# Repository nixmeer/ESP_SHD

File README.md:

# ESP_SmartHomeDevice
Keep it simple and stupid. Everyone should be able to build his or her smart home device (SHD).
## What this project is supposed to do:
This code runs on ESP8266 and is optimized to work together with [HomeBridge](https://github.com/nfarina/homebridge) and [mqttthing](https://github.com/arachnetech/homebridge-mqttthing)
- [x] create an easy to use platform that uses wifi and mqtt to talk to [mqttthing](https://github.com/arachnetech/homebridge-mqttthing)
- [ ] print json-config-code for homebridge-mqttthing
- [ ] create a webserver and a settings class that allow setup via GUI
## Supported devices
- [x] Stateless switches
- [x] TMP36 sensors
- [x] DHT22 temperature and humidity sensors
- [x] Motion sensors
- [x] Single color PWM light
- [x] Temperature PWM light
- [x] WS2512b strips
- [x] Sprinkler
- [x] Relay/Switch
- [x] Window blinds
## Libraries and cores used
- [Arduino core for ESP8266 WiFi chip](https://github.com/esp8266/Arduino) (v2.4.2)
- [pubSubClient](https://github.com/knolleary/pubsubclient) by knolleary (v2.7.0)
- [FastLED](https://github.com/FastLED/FastLED) by FastLED (v3.3.2)
- [WiFiManager](https://github.com/tzapu/WiFiManager) by tzapu (v0.15.0)
- [ESP8266_new_pwm](https://github.com/StefanBruens/ESP8266_new_pwm) by StefanBruens (included)
## Code Structure
There is a separate class for each device. Every device is implemented as a child class of ESP_SmartHomeDevice. After initializing ESP_SmartHomeDevice, objects of these classes may be created. All of these objects use one common mqtt client provided by ESP_SmartHomeDevice. Each child class of ESP_SmartHomeDevice has to implement the following member functions:
- `bool handleMqttRequest(char * _topic, unsigned char * _payload, uint16_t _length)` is being called after a request has been pushed to the mqtt client
- `void resubscribe()` is being called after the connection to the mqtt broker was lost
- `void timer5msHandler()` is being called every 5 ms
## Basic usage in Arduino
```
ESP_SmartHomeDevice::init(const char* _mqttServerAddress, uint16_t _port, char* _name);
ESP_SmartHomeDevice::init(char* _name)
```
Call `ESP_SmartHomeDevice::init(...)` to setup and initialize wifi and mqtt in the `setup()` function of your *.ino* file. If there is no known wifi network, a wifi access point will be created which lets you connect the ESP to a wifi network. If you use **one** local mqtt broker and it is discoverable via mDNS, call `ESP_SmartHomeDevice::init(char* _name)`. The SHD then automatically connects to it. If it discovers 0 or more than one, it resets itself.
Now just create new devices using `new Shd...()`.
MQTT topics do always begin with the `_name` parameter initialized here.
## Creating devices
### Motion Sensor
To add a motion sensor, just call `new ShdMotionSensor(uint8_t _pin)`. It publishes it's status (`true` or `false` as char) to `_name/Motion`.
### Temperature Sensor
To add a temperature sensor, just call `new ShdTmp36Sensor()`. No pin is needed, since there is only one ADC available in the ESP8266. It publishes the temperature to `_name/Temperature`.
### WS2812b strip
Only stips at pin 4 are Supported.
Call ` ShdWs2812bStrip::initStrip(uint16_t _numberOfLeds, uint16_t _updateInterval)`. First argument sets the number of LEDs of the entire strip, second argument sets the update interval for the strip in milliseconds. 41 ms (24 fps) looked jerky, 25 ms (40 fps) looks much better.
Call `new ShdWs2812bStrip(uint16_t _firstLed, uint16_t _lastLed, uint16_t _ignitionPoint, ignitionDirection _ignitionDirection, uint8_t _hopsPerShow, uint8_t _flankLength)` to create a light section, multiple can be created for one strip and be used simultaneously. These sections can overlap (not yet tested).
- `_firstLed` is this section's first LED (value 1 or greater)
- `_lastLed` is this section's last LED (less or equal to `_numberOfLeds`)
- `_ignitionPoint` is the LED that all effects start from
- `_ignitionDirection` is `IGNITION_SINGLE_FORWARD`, `IGNITION_SINGLE_BACKWARD`, `IGNITION_BOTH_FORWARD` or `IGNITION_BOTH_BACKWARD`
- `_hopsPerShow` is the number of LEDs that the turn-on effect is shifted each frame. This has an impact on the effects speed.
- `_flankLength` sets the number of LEDs that are needed to transfer from one color to another
ShdWs2812bStrip subscribes to `_name/Lamp/_sectionNumber/setColor` and `_name/Lamp/_sectionNumber/setStatus`. `_sectionNumber`is increased for every new section starting at 1.
ShdWs2812bStrip publishes its status (0 and 1) to `_name/Lamp/_sectionNumber/getStatus`, its color to `_name/Lamp/_sectionNumber/getColor` and publishes its brightness to `_name/Lamp/_sectionNumber/getBrightness`.
### Button
To add a new button, call `new ShdButton(uint8_t _pin, bool _lowActive, uint32_t _millisDebounce, uint32_t _millisLongClick, uint32_t _millisMultiClick)`. It publishes to `_name/Button/_buttonNumber`. It detects single clicks ("1"), double clicks("2") and long presses ("L"). `_buttonNumber` is increased for every new button starting at 1.
### Relay
To ad a new relay, use `new ShdRelay(uint8_t _pin, uint32_t _millisBetweenToggle, bool _lowActive)`. It subscribes `_name/Relay/_relayNumber/setStatus` where `_name` is the device name and `_relayNumber` counts the created relays starting at 1. It publishes its status to `_name/Relay/_relayNumber/getStatus`. `_millisBetweenToggle` sets the minimum time between to toggles avoiding the relay to be switched to quickly.
# Hardware
This repository contains the eagle and gerber files of my SHD hardware. The PCBs can be ordered from jlcpcb.com or any other pcb manufacturer. The following parts are necessary for a basic assembly:
- ESP12f module
- XC6206 voltage regulator
- 3 resistors (10k0)
- pinheader (7 pins)
To programm the ESP8266, you can use any 3.3 V FTDI board. I use the ESP01-flasher and created a adapter cable using jumper wires and heat shrink tubing. Note: most ESP01-flashers need to have a GND connection to GPIO 0 added to put the ESP8266 to flash mode.
# mosquitto broker on raspberry pi
You can use any mqtt broker with this code. In order to have all devices run stable and reconnect after a loss of power, it's recommended to use mDNS to expose the mqtt broker service to the network, so all SHDs can automatically connect to it. After installing mosquitto on the raspberry pi, call `sudo nano /etc/avahi/services/mqtt.service`. Fill the following:
```
<?xml version="1.0" standalone='no'?>
<!DOCTYPE service-group SYSTEM "avahi-service.dtd">
<service-group>
 <name replace-wildcards="yes">MQTT on %h</name>
  <service>
   <type>_mqtt._tcp</type>
   <port>1883</port>
  </service>
</service-group>
```
Then reboot. SHDs should find the broker now automatically.

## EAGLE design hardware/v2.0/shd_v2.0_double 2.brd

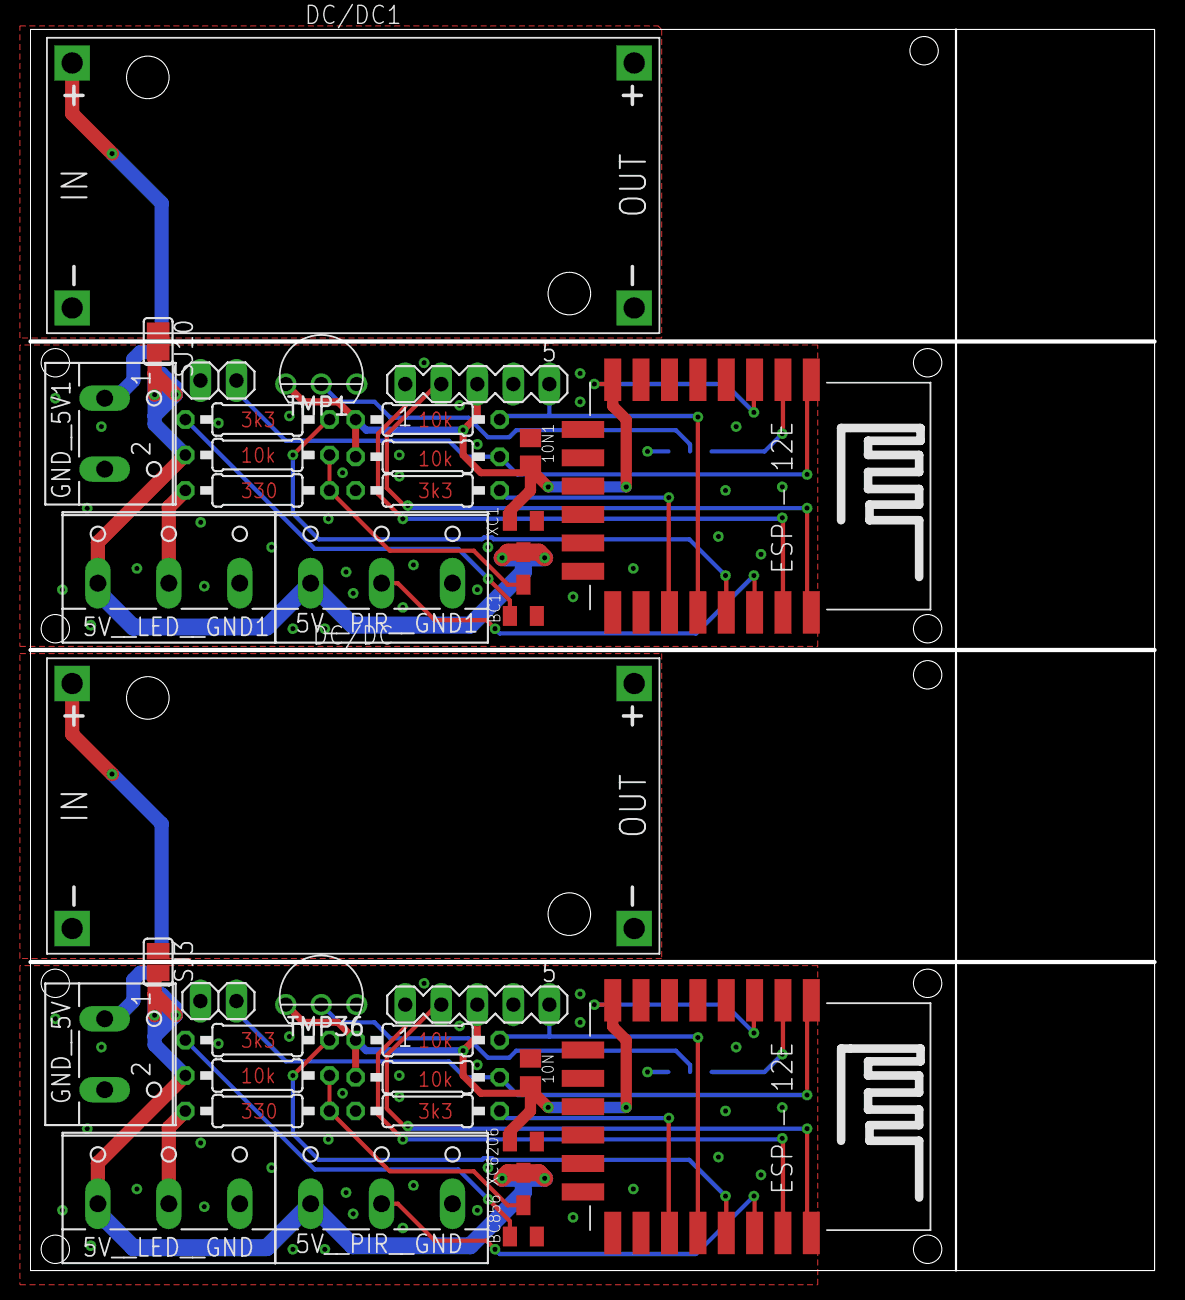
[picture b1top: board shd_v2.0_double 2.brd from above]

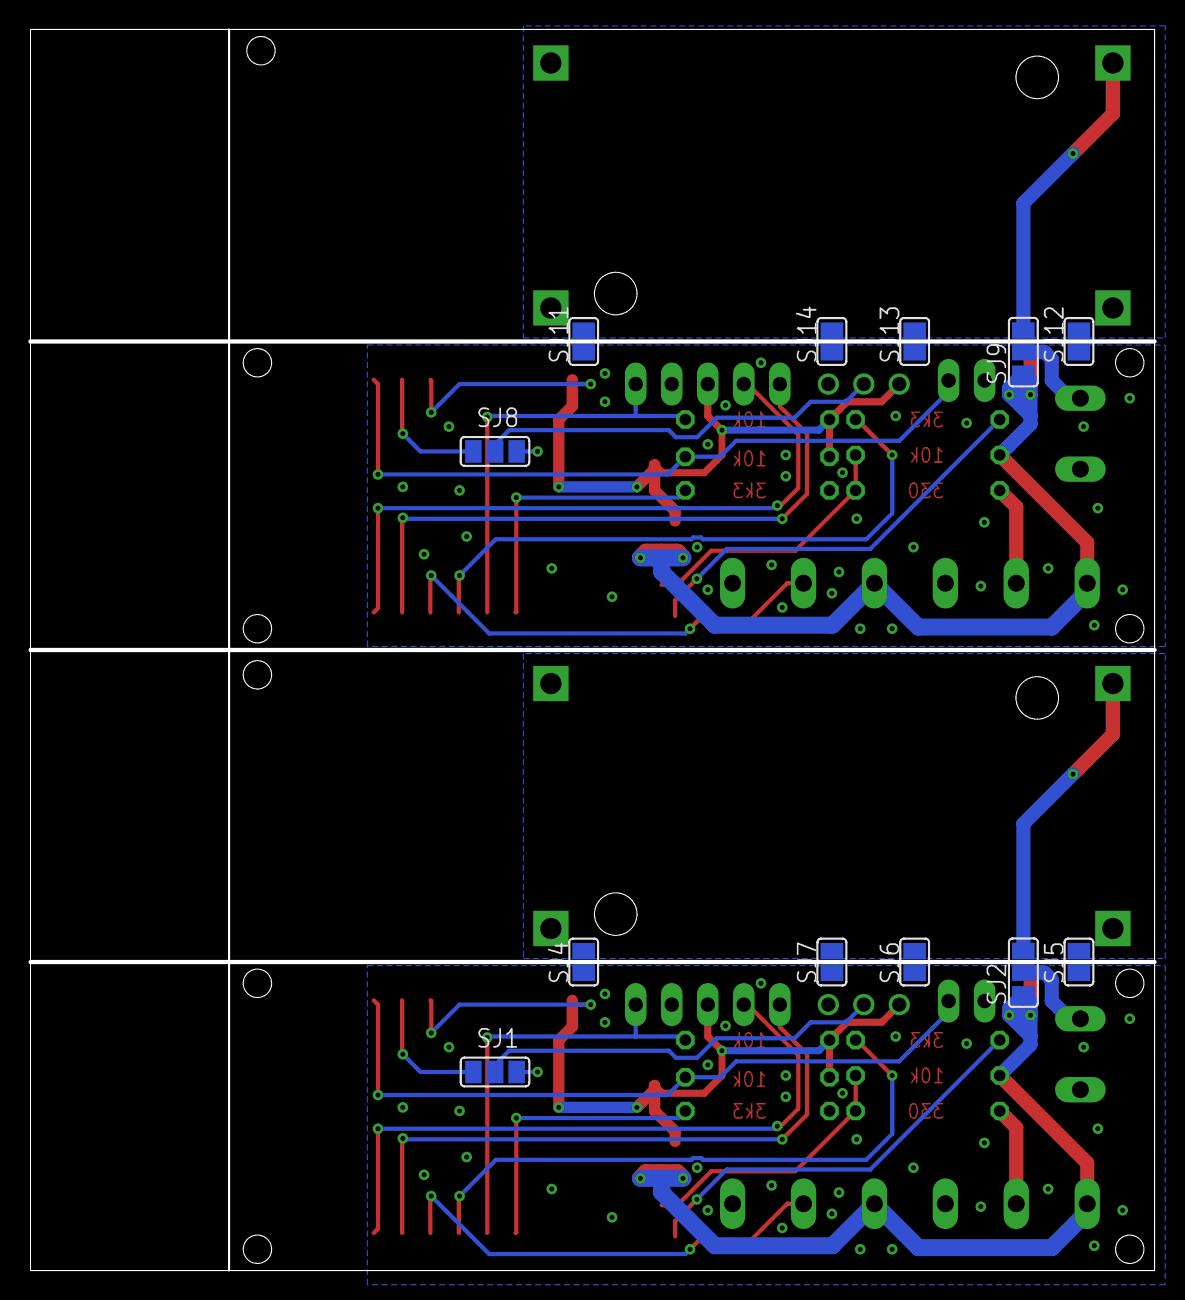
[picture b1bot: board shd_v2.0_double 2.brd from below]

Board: 2 copper layers, 79.2 x 87.4 mm, 48 parts (12 on the bottom side), 38 nets.

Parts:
5V__LED__GND, 5V__LED__GND1, 5V__PIR__GND, 5V__PIR__GND1: W237-103
10N, 10N1: C0805
BC1, BC856: SOT23-BEC
DC/DC, DC/DC1: DC-DC-STEP-DOWN-LM2596
GND__5V, GND__5V1: W237-102
JP1, JP2: 1X02
PROG_INTERFACE, PROG_INTERFACE1: MA05-1
R_GPIO1, R_GPIO2: 3k3; 0207/10
R_LED_B, R_LED_B1: 3k3; 0207/10
R_LED_C, R_LED_C2: 10k; 0207/10
R_LED_C1, R_LED_C3: 330; 0207/10
R_PROG, R_PROG1: 10k; 0207/10
R_RST, R_RST1: 10k; 0207/10
SJ1, SJ2, SJ8, SJ9: SJ_2
SJ3, SJ4, SJ5, SJ6, SJ7, SJ10, SJ11, SJ12, SJ13, SJ14: SJ
TMP1, TMP36: TMP36; TO-92
U1, U2: ESP12E-SMD
XC1, XC6206: SOT23

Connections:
GND: 5V__LED__GND.3, 5V__PIR__GND.3, 10N.2, BC856.E, GND__5V.2, JP1.1, PROG_INTERFACE.4, SJ4.1, SJ5.1, SJ6.1, SJ7.1, TMP36.3, U1.GND, U1.GPIO15, XC6206.1
GND1: 5V__LED__GND1.3, 5V__PIR__GND1.3, 10N1.2, BC1.E, GND__5V1.2, JP2.1, PROG_INTERFACE1.4, SJ11.1, SJ12.1, SJ13.1, SJ14.1, TMP1.3, U2.GND, U2.GPIO15, XC1.1
GND_STEP_DOWN: DC/DC.IN-, DC/DC.OUT-, SJ4.2, SJ5.2, SJ6.2, SJ7.2
GND_STEP_DOWN1: DC/DC1.IN-, DC/DC1.OUT-, SJ11.2, SJ12.2, SJ13.2, SJ14.2
GPIO0: PROG_INTERFACE.5, R_PROG.1, U1.GPIO0
GPIO1: PROG_INTERFACE1.5, R_PROG1.1, U2.GPIO0
LED_DATA_3.1: R_LED_B1.2, U2.GPIO4
LED_DATA_3.3: R_LED_B.2, U1.GPIO4
LED_DATA_3.3_R: BC856.B, R_LED_B.1
LED_DATA_3.3_R1: BC1.B, R_LED_B1.1
LED_DATA_5.0: BC856.C, R_LED_C.1, R_LED_C1.2
LED_DATA_5.1: BC1.C, R_LED_C2.1, R_LED_C3.2
LED_DATA_OUT: 5V__LED__GND.2, R_LED_C1.1
LED_DATA_OUT1: 5V__LED__GND1.2, R_LED_C3.1
unnamed: R_GPIO1.2, U2.GPIO2
unnamed: R_GPIO2.2, U1.GPIO2
PIR: 5V__PIR__GND.2, U1.GPIO5
PIR1: 5V__PIR__GND1.2, U2.GPIO5
RST: JP1.2, R_RST.1, U1.RESET
RST1: JP2.2, R_RST1.1, U2.RESET
RX: PROG_INTERFACE.1, U1.RXD0
RX1: PROG_INTERFACE1.1, U2.RXD0
TMP_ANA: SJ1.1, U1.ADC
TMP_ANA1: SJ8.1, U2.ADC
TX: PROG_INTERFACE.2, U1.TXD0
TX1: PROG_INTERFACE1.2, U2.TXD0
VCC_5.0: 5V__LED__GND.1, 5V__PIR__GND.1, R_LED_C.2, SJ2.1, SJ3.2, XC6206.3
VCC_5.1: 5V__LED__GND1.1, 5V__PIR__GND1.1, R_LED_C2.2, SJ9.1, SJ10.2, XC1.3
VCC_STEP_DOWN: DC/DC.OUT+, SJ3.1
VCC_STEP_DOWN1: DC/DC1.OUT+, SJ10.1
VDD_3.1: 10N1.1, PROG_INTERFACE1.3, R_PROG1.2, R_RST1.2, TMP1.1, U2.CH_PD, U2.VCC, XC1.2
VDD_3.3: 10N.1, PROG_INTERFACE.3, R_PROG.2, R_RST.2, TMP36.1, U1.CH_PD, U1.VCC, XC6206.2
V_IN: GND__5V.1, SJ2.2
V_IN1: GND__5V1.1, SJ9.2
V_IN_1: DC/DC.IN+, SJ2.3
V_IN_2: DC/DC1.IN+, SJ9.3
V_TMP: SJ1.2, TMP36.2
V_TMP1: SJ8.2, TMP1.2

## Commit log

2018-10-12 Letzten Stand widerherstellen
2018-10-13 Added repeated timer functions to get the mqtt client to work. MQTT broker issue still occur.
2018-10-16 Motion Sensor funktioniert mit Homebridge in HomeKit
2018-10-18 Everything tested. Reconnecting won't work for some reason.
2018-10-18 Testcommit
2018-10-18 Test rückgängig
2018-10-18 Tried to get the reconnecting to mqtt broker to work. Worked when calling ESP_SmartHomeDevice::loop() from Arduino loop
2018-10-20 - Added temperature sensor TMP36 support - ESP_SmartHomeDevice::loop() now called by Arduino loop() until os_timer_t works
2018-10-23 added "ms" to the debug output
2018-11-26 Starting to add WS2812b support
2018-12-04 Changed Callback Parameters to work with strcmp and strtok (unsigned char* instead of byte*)
2018-12-04 Erase most compiler errors.
2018-12-04 Changed handleMqttRequest's parameters to work with strcmp() and strtok()
2018-12-11 First test runs of WS2812b completed. Still debugging.
2018-12-15 Bug fixes in ShdWS2812b lib
2018-12-19 Added description in Readme.md Bug fixes
2018-12-21 Added Support for a mqtt button. It detects single, double and long clicks.
2018-12-21 Started creating a settings class that holds all changeable values (might be displayed in a GUI for easy setup).
2018-12-22 Integrated wifi ESP setup to ESP_SmartHomeDevice::init()
2018-12-22 Fixed an issue that turning the strip off would change the direction of the light moving in
2018-12-22 bug fixes for wifi setup
2018-12-22 Document fix
2018-12-29 Added PWM Light support using ESP8266_new_pwm by Stefan Brüns
2018-12-31 Pwm Light now debugged and working
2018-12-31 code styling
2018-12-31 Some changes to reconnecting MQTT, not finally solved yet.
2019-01-07 Bug fix that caused mqtt publishing issues if reconnecting after mqtt broker failure
2019-01-12 Removed free heap info on serial
2019-01-12 added support for IPAddress to connect to mqtt broker instead of hostname. mDNS now uses IPAddresses
2019-01-12 adds gamma correction. fixes an issue which caused the ws2812b strip to turn on white always.
2019-01-12 Changed from Shd_PwmLight() to ShdPwmLight
2019-01-12 support for up to 8 SHDs
2019-01-12 now shows example usage for all supported devices
2019-02-03 Added support for republishing device's current status after reconnecting to MQTT
2019-02-03 - updates char array sizes - reduces size of gamma correction array - adds support for republishing after reconnecting to MQTT broker
2019-02-03 - improves 5ms timer call - adds support for republishing after reconnecting to MQTT broker
2019-02-03 - improves update interval - adds support for republishing after reconnecting to MQTT broker - show() is now called by the highest section number, not number 1
2019-02-13 adds global debug-define and minor bug fixes
2019-02-13 adds colored firstLed, ignitionPoint and lastLed when debugging. changes for ignitionPoint: needs to be greater equal than firstLed and less equal than lastLed
2019-03-09 fixes a bug in mqtt connection progress
2019-03-09 Bug fixes
2019-03-09 adds hardware files to repo
2019-04-30 adds support for DS18B20 temperature sensors and renames ShdTemperatureSensor to ShdTmp36
2019-04-30 adds button support
2019-04-30 renames ShdTemperatureSensor to ShdTmp36Sensor
2019-04-30 updates new temperature sensor naming
2019-04-30 cleans the hardware directory
2019-04-30 adds sprinkler and renames the temperature sensor
2019-04-30 corrects debug output
2019-04-30 no message
2019-04-30 adds sprinkler support
2019-04-30 removes the use of "MDNS.begin(name)" method
2019-04-30 adds a toggle function
2019-05-08 no change
2019-09-30 minor changes and bug fixes
2019-09-30 minor changes
2020-02-10 adds multiple bug fixes
2020-02-10 iCloud stuff
2020-02-13 adds support for relays
2020-02-13 fixes a bug with wrong naming
2020-02-13 resets ShdPwmLight to october 2019
2020-02-13 adds bug fixes and a compilable relay class
2020-03-07 improves debug messages
2020-03-07 adapts new mqtt style
2020-03-07 lets you choose to start at on or off after boot
2020-03-07 bug fix
2020-03-07 removes unnecessary line
2020-03-08 fixes an issue with the parent class
2020-03-08 adds info for relay
2020-03-09 re-adds *.brd-hardware-files
2020-03-09 adds 2nd generation hardware to this project. This hardware has an additional step down converter that lets you use any power supply. However, the part of the pcb holding the step down converter can 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
2020-03-30 adds hardware v2.0 and software support for dht22 sensor
2020-04-01 hardware updates
2020-05-02 adds hardware v2.1
2020-06-01 adds debugged DHTxx support
2020-06-01 shifts pwm handling to ESP_SmartHomeDevice in order to have multiple different classes (such as SHD_PwmLight and SHD_PwmLightTemperature) to use pwm code
2020-07-11 adds support for temperature pwm light
2020-07-11 updates readme
2020-07-12 adds second mode for pwmTemperatureLight
2020-07-12 Adds contact sensor
2020-07-25 Bug fixes.
2021-03-22 restructures some files
2021-03-22 add window blinds (relays)
2021-03-22 removes files that are no longer needed
2021-03-22 updates comment
2021-04-02 adds working WindowBlindRelay
2025-03-22 minor fixes

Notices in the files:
parts and their libraries:
diy-modules: Released under the Creative Commons Attribution 4.0 International License: http://creativecommons.org/licenses/by/4.0
